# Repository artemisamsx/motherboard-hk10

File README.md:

# Artemisa MSX - Model HK-10 Motherboard

This repository contains the KiCad project files for the Model HK-10 motherboard, part of the **Artemisa** project.

## About Artemisa

Artemisa is a project to design new MSX-1 compatible computers using modern manufacturing
techniques while staying true to the original architecture: a Z80 CPU, discrete memory chips,
and dedicated peripheral ICs (VDP, PSG, PPI, etc.), with no FPGAs involved. The roadmap
includes several different models, each exploring different trade-offs between fidelity,
cost, and ease of assembly.

## The HK-10 model

The HK-10 is based on the **Model 101**, a prototype that was never distributed commercially.
The goal of the HK-10 is to bring that design to the general public as a homebrew-friendly
product, with the constraints and trade-offs typical of the homebrew scene.

"HK" stands for **Homebrew Kit**. The HK-10 is meant to be sold as a kit and assembled by the
user, comprising:

- The motherboard and other PCBs
- A 3D-printed PETG enclosure
- The main chips (CPU, memory, PSG, VDP)
- Passive components (resistors, capacitors, etc.)

### Features

- 2 cartridge slots
- 1 datasette (cassette) port
- 2 joystick ports
- External, cable-connected keyboard port

The HK-10 does **not** include a serial port or a printer port.

### Graphics

The graphics subsystem is implemented on separate PCBs rather than being part of the
motherboard itself, so that users can customize their video output and choose a graphics
chip (TMS9918 vs TMS9928 vs TMS9929). These graphics cards are based on the GFX-9918 card
used in the Model 101 prototype, but with a different form factor and naming, e.g.
`HKG-9918`, `HKG-9929`.

### Memory

The HK-10 uses SRAM instead of DRAM. For the memory sizes involved, SRAM is simpler, cheaper
and easier to source than DRAM, at the cost of some board space.

### Design philosophy

The HK-10 aims to be the simplest and most didactic model in the Artemisa lineup. To that
end, it avoids any programmable logic devices (PLDs, PALs, GALs, etc.) in favor of discrete
logic chips, consistent with how the original MSX computers were designed in the 1980s.

### Differences from the Model 101 prototype

- **Form factor**: the HK-10 uses a different, more compact form factor than the 101.
- **Power supply**: the HK-10 has its own integrated AC/DC adapter providing 5V, 12V and -12V,
  whereas the 101 was only powered externally at 5V.
- **Simplified circuits**: some circuits have been simplified compared to the 101, namely the
  clock generation and the power-on reset (PoR) circuit.
- **No integrated keyboard**: unlike most MSX computers (and most microcomputers of that era),
  the HK-10 does not have a keyboard built into the case. The keyboard is a separate unit
  connected via cable to a port on the motherboard.

## Repository layout

The schematic is split into sheets by functional block:

| File | Contents |
|---|---|
| `motherboard-hk10.kicad_sch` | Top-level sheet |
| `cpu.kicad_sch` | Z80 CPU |
| `ram.kicad_sch` | SRAM |
| `rom.kicad_sch` | ROM |
| `ppi.kicad_sch` | Programmable Peripheral Interface (keyboard, joysticks, cassette control) |
| `psg.kicad_sch` | Programmable Sound Generator |
| `clock.kicad_sch` | Clock generation |
| `decoding.kicad_sch` | Address decoding |
| `power.kicad_sch` | Power supply and power-on reset |
| `slots.kicad_sch` | Cartridge slots |
| `keyboard.kicad_sch` | External keyboard connector |
| `cassette.kicad_sch` | Datasette port |

`motherboard-hk10.kicad_pcb` contains the PCB layout, and `simulation/` contains SPICE
simulations used to validate specific circuits (power-on reset, clock generation, video
output filtering, etc.).

See [CHANGELOG.md](CHANGELOG.md) for a history of board revisions.

## Key components

- **Clock generator**: [Epson SG-615P / SG-531P][1], a packaged crystal oscillator (SPXO)
  used to generate the master clock.

## License

This project is licensed under the [TAPR Open Hardware License](LICENSE.txt).

---

[1]: https://www.mouser.com/datasheet/2/137/SG_615P_en-1880245.pdf "Epson SG-615P / SG-531P datasheet"

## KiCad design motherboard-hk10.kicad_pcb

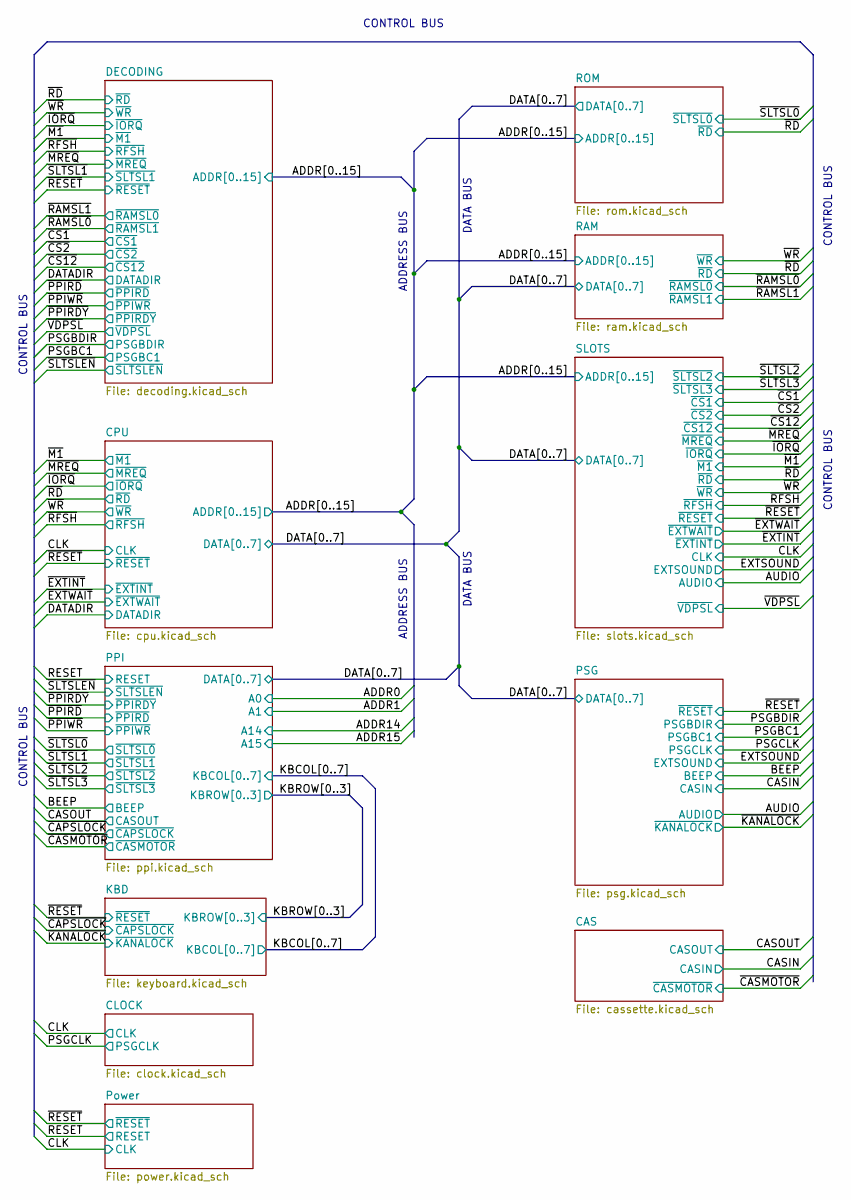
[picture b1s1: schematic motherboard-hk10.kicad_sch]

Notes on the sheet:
CONTROL BUS
ADDRESS BUS
DATA BUS

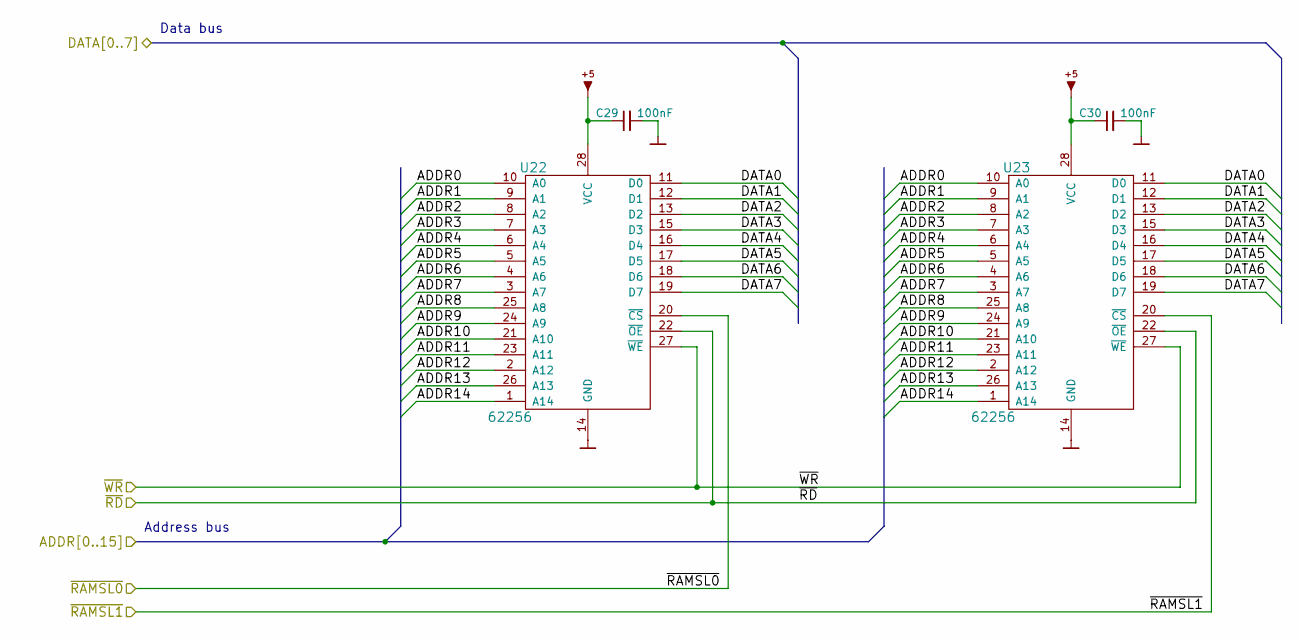
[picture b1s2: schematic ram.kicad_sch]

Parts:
C29, C30: 100nF; C_Disc_D5.0mm_W2.5mm_P2.50mm
U22, U23: 62256; DIP-28_W15.24mm_Socket

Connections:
/ADDR0: U22.10 (A0), U23.10 (A0); also elsewhere on the board
/ADDR1: U22.9 (A1), U23.9 (A1); also elsewhere on the board
/ADDR2: U22.8 (A2), U23.8 (A2); also elsewhere on the board
/ADDR3: U22.7 (A3), U23.7 (A3); also elsewhere on the board
/ADDR4: U22.6 (A4), U23.6 (A4); also elsewhere on the board
/ADDR5: U22.5 (A5), U23.5 (A5); also elsewhere on the board
/ADDR6: U22.4 (A6), U23.4 (A6); also elsewhere on the board
/ADDR7: U22.3 (A7), U23.3 (A7); also elsewhere on the board
/ADDR8: U22.25 (A8), U23.25 (A8); also elsewhere on the board
/ADDR9: U22.24 (A9), U23.24 (A9); also elsewhere on the board
/ADDR10: U22.21 (A10), U23.21 (A10); also elsewhere on the board
/ADDR11: U22.23 (A11), U23.23 (A11); also elsewhere on the board
/ADDR12: U22.2 (A12), U23.2 (A12); also elsewhere on the board
/ADDR13: U22.26 (A13), U23.26 (A13); also elsewhere on the board
/ADDR14: U22.1 (A14), U23.1 (A14); also elsewhere on the board
/DATA0: U22.11 (D0), U23.11 (D0); also elsewhere on the board
/DATA1: U22.12 (D1), U23.12 (D1); also elsewhere on the board
/DATA2: U22.13 (D2), U23.13 (D2); also elsewhere on the board
/DATA3: U22.15 (D3), U23.15 (D3); also elsewhere on the board
/DATA4: U22.16 (D4), U23.16 (D4); also elsewhere on the board
/DATA5: U22.17 (D5), U23.17 (D5); also elsewhere on the board
/DATA6: U22.18 (D6), U23.18 (D6); also elsewhere on the board
/DATA7: U22.19 (D7), U23.19 (D7); also elsewhere on the board
/~RAMSL0: U22.20 (~CS); also elsewhere on the board
/~RAMSL1: U23.20 (~CS); also elsewhere on the board
/~RD: U22.22 (~OE), U23.22 (~OE); also elsewhere on the board
/~WR: U22.27 (~WE), U23.27 (~WE); also elsewhere on the board
GND: C29.2, C30.2, U22.14 (GND), U23.14 (GND); also elsewhere on the board
VCC: C29.1, C30.1, U22.28 (VCC), U23.28 (VCC); also elsewhere on the board

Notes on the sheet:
Data bus
Address bus

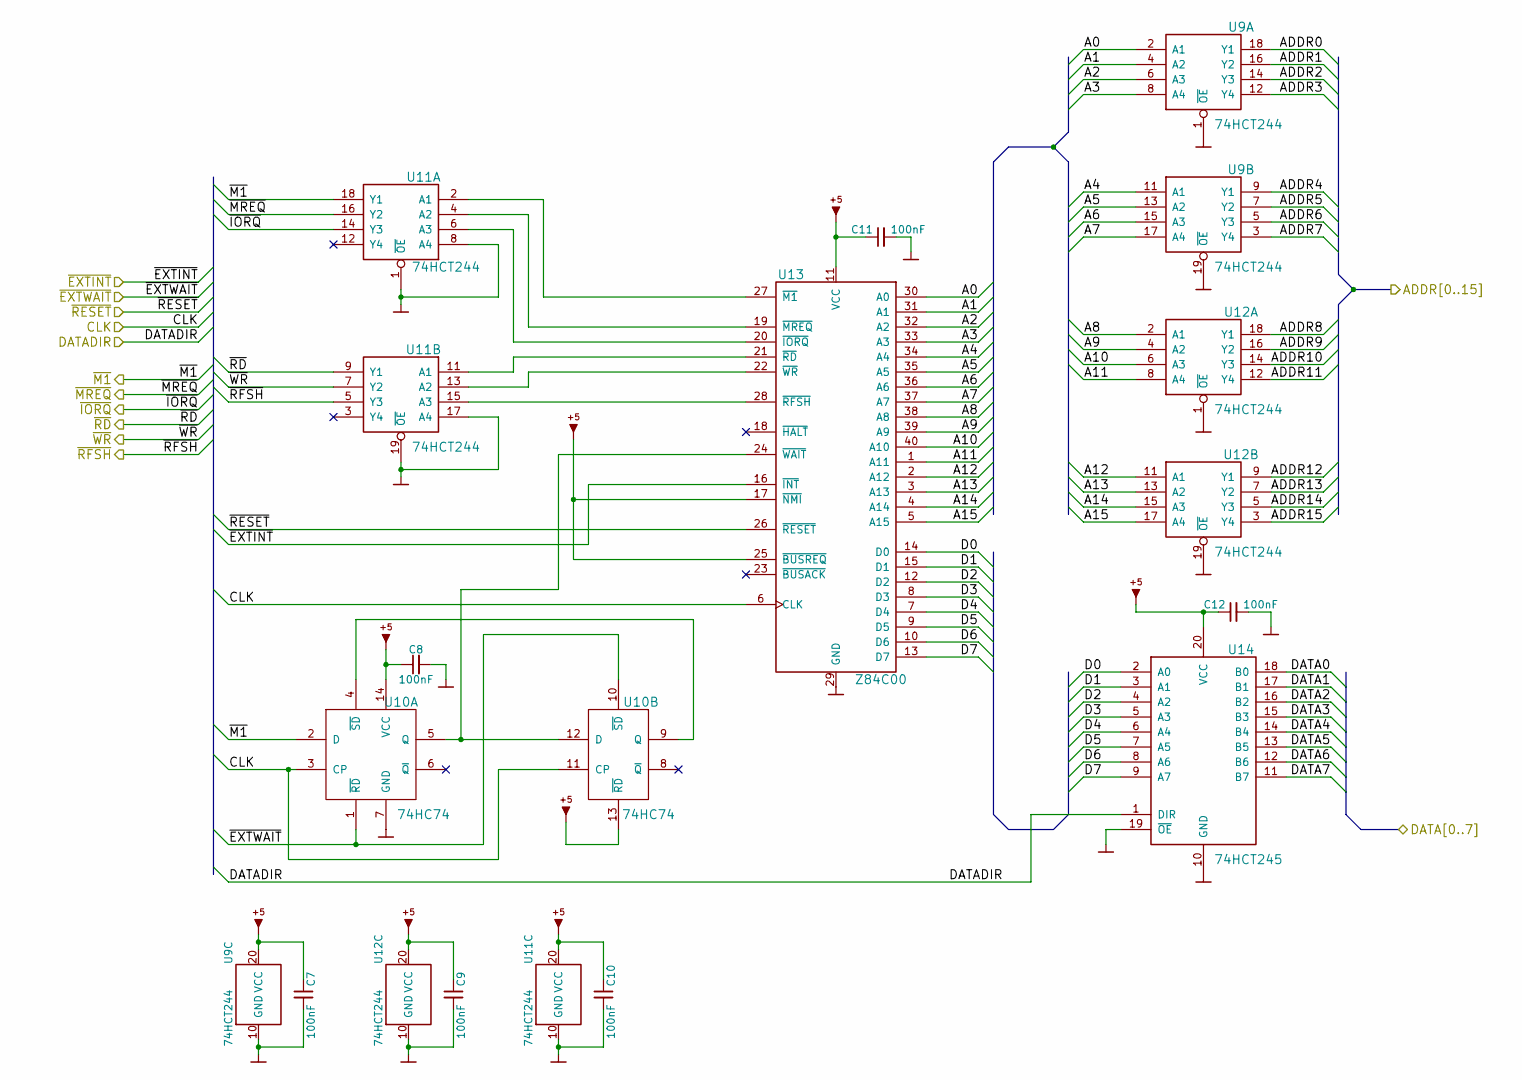
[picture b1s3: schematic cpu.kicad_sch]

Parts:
C7, C8, C9, C10, C11, C12: 100nF; C_Disc_D5.0mm_W2.5mm_P2.50mm
U9, U11, U12: 74HCT244; DIP-20_W7.62mm
U10: 74HC74; DIP-14_W7.62mm
U13: Z84C00; DIP-40_W15.24mm_Socket
U14: 74HCT245; DIP-20_W7.62mm

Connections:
/ADDR0: U9.18 (Y1); also elsewhere on the board
/ADDR1: U9.16 (Y2); also elsewhere on the board
/ADDR2: U9.14 (Y3); also elsewhere on the board
/ADDR3: U9.12 (Y4); also elsewhere on the board
/ADDR4: U9.9 (Y1); also elsewhere on the board
/ADDR5: U9.7 (Y2); also elsewhere on the board
/ADDR6: U9.5 (Y3); also elsewhere on the board
/ADDR7: U9.3 (Y4); also elsewhere on the board
/ADDR8: U12.18 (Y1); also elsewhere on the board
/ADDR9: U12.16 (Y2); also elsewhere on the board
/ADDR10: U12.14 (Y3); also elsewhere on the board
/ADDR11: U12.12 (Y4); also elsewhere on the board
/ADDR12: U12.9 (Y1); also elsewhere on the board
/ADDR13: U12.7 (Y2); also elsewhere on the board
/ADDR14: U12.5 (Y3); also elsewhere on the board
/ADDR15: U12.3 (Y4); also elsewhere on the board
/CLK: U10.3 (CP), U10.11 (CP), U13.6 (CLK); also elsewhere on the board
/CPU/A0: U9.2 (A1), U13.30 (A0)
/CPU/A1: U9.4 (A2), U13.31 (A1)
/CPU/A2: U9.6 (A3), U13.32 (A2)
/CPU/A3: U9.8 (A4), U13.33 (A3)
/CPU/A4: U9.11 (A1), U13.34 (A4)
/CPU/A5: U9.13 (A2), U13.35 (A5)
/CPU/A6: U9.15 (A3), U13.36 (A6)
/CPU/A7: U9.17 (A4), U13.37 (A7)
/CPU/A8: U12.2 (A1), U13.38 (A8)
/CPU/A9: U12.4 (A2), U13.39 (A9)
/CPU/A10: U12.6 (A3), U13.40 (A10)
/CPU/A11: U12.8 (A4), U13.1 (A11)
/CPU/A12: U12.11 (A1), U13.2 (A12)
/CPU/A13: U12.13 (A2), U13.3 (A13)
/CPU/A14: U12.15 (A3), U13.4 (A14)
/CPU/A15: U12.17 (A4), U13.5 (A15)
/CPU/D0: U13.14 (D0), U14.2 (A0)
/CPU/D1: U13.15 (D1), U14.3 (A1)
/CPU/D2: U13.12 (D2), U14.4 (A2)
/CPU/D3: U13.8 (D3), U14.5 (A3)
/CPU/D4: U13.7 (D4), U14.6 (A4)
/CPU/D5: U13.9 (D5), U14.7 (A5)
/CPU/D6: U13.10 (D6), U14.8 (A6)
/CPU/D7: U13.13 (D7), U14.9 (A7)
/DATA0: U14.18 (B0); also elsewhere on the board
/DATA1: U14.17 (B1); also elsewhere on the board
/DATA2: U14.16 (B2); also elsewhere on the board
/DATA3: U14.15 (B3); also elsewhere on the board
/DATA4: U14.14 (B4); also elsewhere on the board
/DATA5: U14.13 (B5); also elsewhere on the board
/DATA6: U14.12 (B6); also elsewhere on the board
/DATA7: U14.11 (B7); also elsewhere on the board
/DATADIR: U14.1 (DIR); also elsewhere on the board
/~EXTINT: U13.16 (~INT); also elsewhere on the board
/~EXTWAIT: U10.1 (~RD), U10.10 (~SD); also elsewhere on the board
/~IORQ: U11.14 (Y3); also elsewhere on the board
/~M1: U10.2 (D), U11.18 (Y1); also elsewhere on the board
/~MREQ: U11.16 (Y2); also elsewhere on the board
/~RD: U11.9 (Y1); also elsewhere on the board
/~RESET: U13.26 (~RESET); also elsewhere on the board
/~RFSH: U11.5 (Y3); also elsewhere on the board
/~WR: U11.7 (Y2); also elsewhere on the board
GND: C7.2, C8.2, C9.2, C10.2, C11.2, C12.2, U9.1 (~OE), U9.10 (GND), U9.19 (~OE), U10.7 (GND), U11.1 (~OE), U11.8 (A4), U11.10 (GND), U11.17 (A4), U11.19 (~OE), U12.1 (~OE), U12.10 (GND), U12.19 (~OE), U13.29 (GND), U14.10 (GND), U14.19 (~OE); also elsewhere on the board
unnamed: U10.5 (Q), U10.12 (D), U13.24 (~WAIT)
unnamed: U10.4 (~SD), U10.9 (Q)
unnamed: U11.2 (A1), U13.27 (~M1)
unnamed: U11.4 (A2), U13.19 (~MREQ)
unnamed: U11.6 (A3), U13.20 (~IORQ)
unnamed: U11.11 (A1), U13.21 (~RD)
unnamed: U11.13 (A2), U13.22 (~WR)
unnamed: U11.15 (A3), U13.28 (~RFSH)
VCC: C7.1, C8.1, C9.1, C10.1, C11.1, C12.1, U9.20 (VCC), U10.13 (~RD), U10.14 (VCC), U11.20 (VCC), U12.20 (VCC), U13.11 (VCC), U13.17 (~NMI), U13.25 (~BUSREQ), U14.20 (VCC); also elsewhere on the board

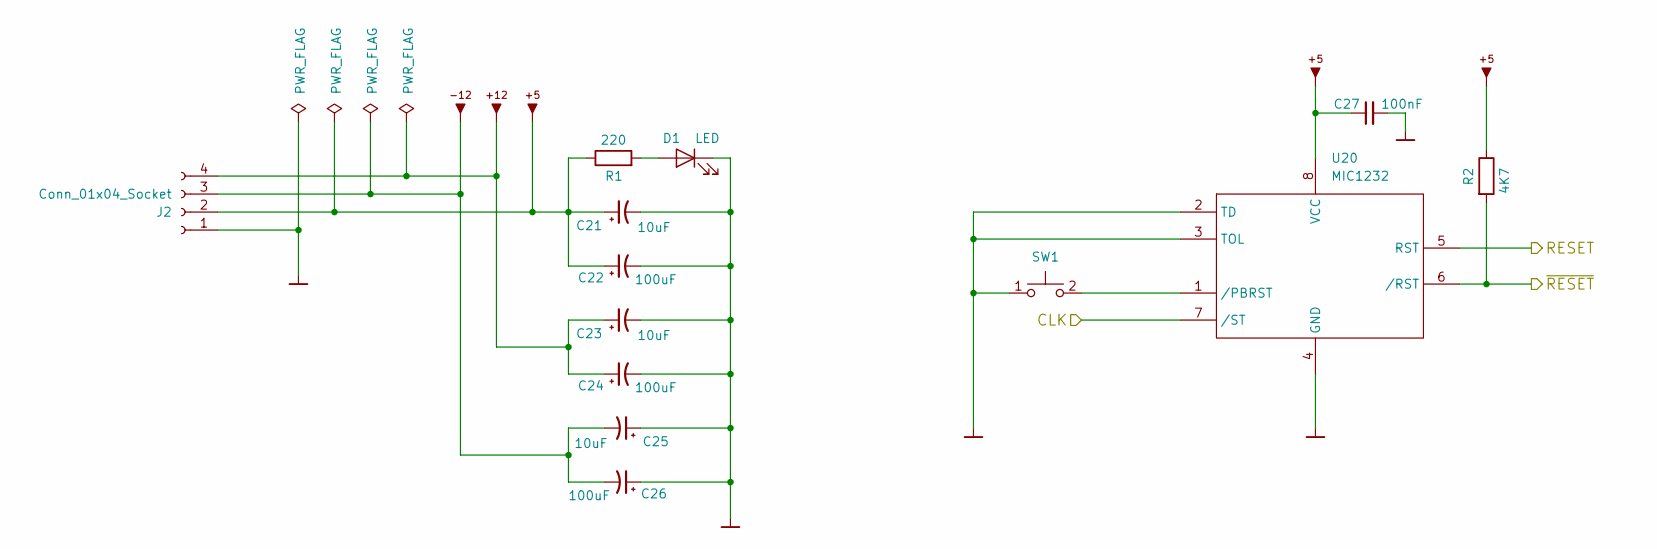
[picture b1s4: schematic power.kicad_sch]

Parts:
C21, C23, C25: 10uF; CP_Radial_D4.0mm_P2.00mm
C22, C24, C26: 100uF; CP_Radial_D5.0mm_P2.50mm
C27: 100nF; C_Disc_D5.0mm_W2.5mm_P2.50mm
D1: LED; PinHeader_1x02_P2.54mm_Vertical
J2: Conn_01x04_Socket; JST_XH_B4B-XH-A_1x04_P2.50mm_Vertical
R1: 220; R_Axial_DIN0207_L6.3mm_D2.5mm_P10.16mm_Horizontal
R2: 4K7; R_Axial_DIN0207_L6.3mm_D2.5mm_P10.16mm_Horizontal
SW1: Push_button; Push_button_angled
U20: MIC1232; DIP-8_W7.62mm

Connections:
12V: C23.1, C24.1, J2.4; also elsewhere on the board
-12V: C25.2, C26.2, J2.3; also elsewhere on the board
/CLK: U20.7 (/ST); also elsewhere on the board
/RESET: U20.5 (RST); also elsewhere on the board
/~RESET: R2.2, U20.6 (/RST); also elsewhere on the board
GND: C21.2, C22.2, C23.2, C24.2, C25.1, C26.1, C27.2, D1.2 (K), J2.1, SW1.1, U20.2 (TD), U20.3 (TOL), U20.4 (GND); also elsewhere on the board
unnamed: D1.1 (A), R1.2
unnamed: SW1.2, U20.1 (/PBRST)
VCC: C21.1, C22.1, C27.1, J2.2, R1.1, R2.1, U20.8 (VCC); also elsewhere on the board

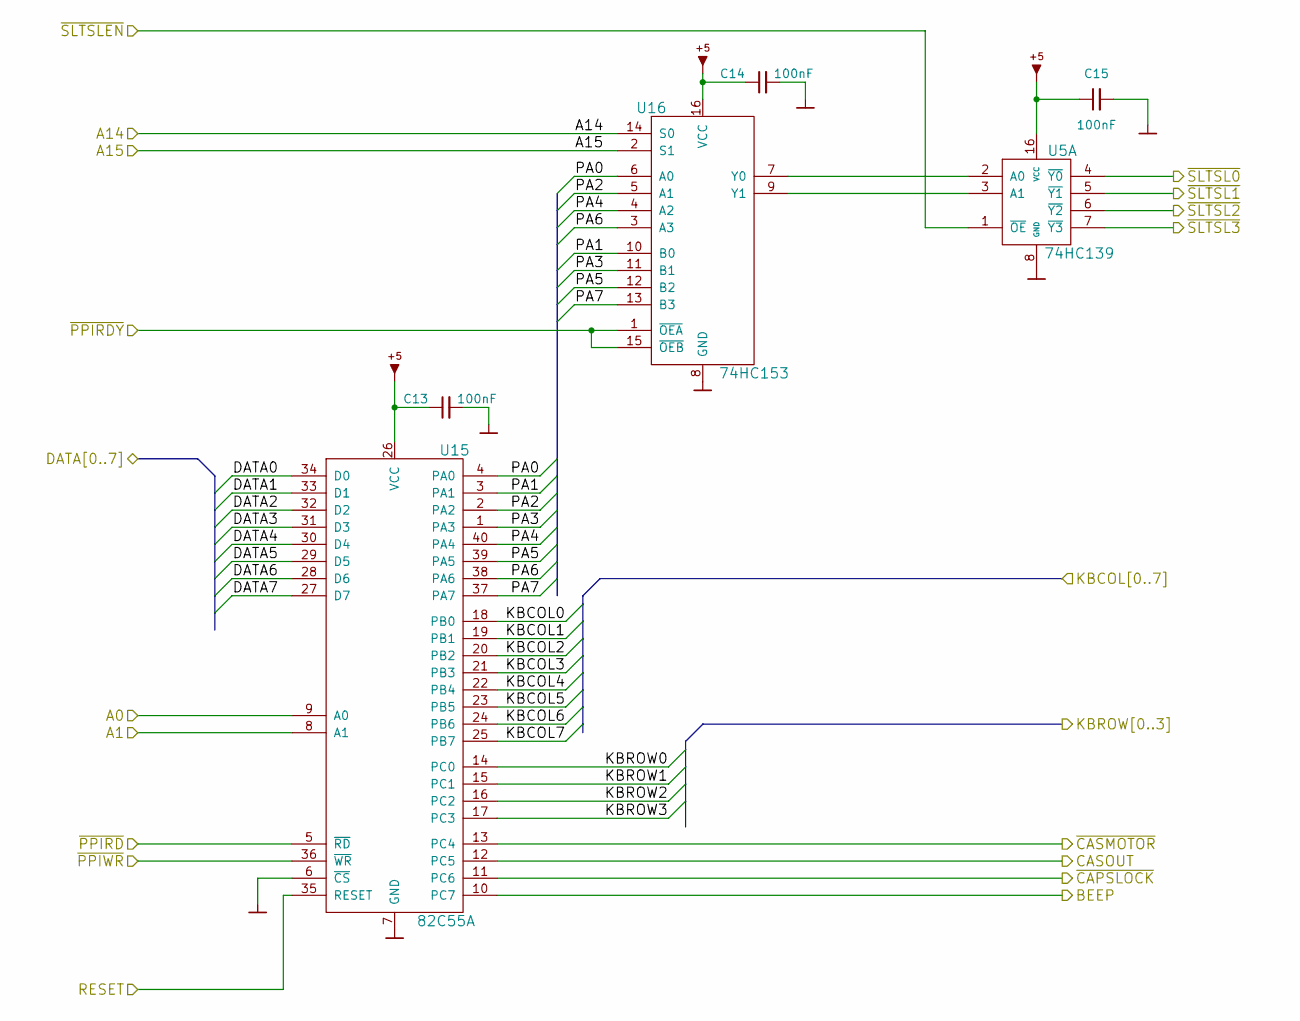
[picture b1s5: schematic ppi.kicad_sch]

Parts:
C13, C14, C15: 100nF; C_Disc_D5.0mm_W2.5mm_P2.50mm
U5: 74HC139; DIP-16_W7.62mm
U15: 82C55A; DIP-40_W15.24mm_Socket
U16: 74HC153; DIP-16_W7.62mm

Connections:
/ADDR0: U15.9 (A0); also elsewhere on the board
/ADDR1: U15.8 (A1); also elsewhere on the board
/ADDR14: U16.14 (S0); also elsewhere on the board
/ADDR15: U16.2 (S1); also elsewhere on the board
/BEEP: U15.10 (PC7); also elsewhere on the board
/CASOUT: U15.12 (PC5); also elsewhere on the board
/DATA0: U15.34 (D0); also elsewhere on the board
/DATA1: U15.33 (D1); also elsewhere on the board
/DATA2: U15.32 (D2); also elsewhere on the board
/DATA3: U15.31 (D3); also elsewhere on the board
/DATA4: U15.30 (D4); also elsewhere on the board
/DATA5: U15.29 (D5); also elsewhere on the board
/DATA6: U15.28 (D6); also elsewhere on the board
/DATA7: U15.27 (D7); also elsewhere on the board
/KBCOL0: U15.18 (PB0); also elsewhere on the board
/KBCOL1: U15.19 (PB1); also elsewhere on the board
/KBCOL2: U15.20 (PB2); also elsewhere on the board
/KBCOL3: U15.21 (PB3); also elsewhere on the board
/KBCOL4: U15.22 (PB4); also elsewhere on the board
/KBCOL5: U15.23 (PB5); also elsewhere on the board
/KBCOL6: U15.24 (PB6); also elsewhere on the board
/KBCOL7: U15.25 (PB7); also elsewhere on the board
/KBROW0: U15.14 (PC0); also elsewhere on the board
/KBROW1: U15.15 (PC1); also elsewhere on the board
/KBROW2: U15.16 (PC2); also elsewhere on the board
/KBROW3: U15.17 (PC3); also elsewhere on the board
/PPI/PA0: U15.4 (PA0), U16.6 (A0)
/PPI/PA1: U15.3 (PA1), U16.10 (B0)
/PPI/PA2: U15.2 (PA2), U16.5 (A1)
/PPI/PA3: U15.1 (PA3), U16.11 (B1)
/PPI/PA4: U15.40 (PA4), U16.4 (A2)
/PPI/PA5: U15.39 (PA5), U16.12 (B2)
/PPI/PA6: U15.38 (PA6), U16.3 (A3)
/PPI/PA7: U15.37 (PA7), U16.13 (B3)
/RESET: U15.35 (RESET); also elsewhere on the board
/~CAPSLOCK: U15.11 (PC6); also elsewhere on the board
/~CASMOTOR: U15.13 (PC4); also elsewhere on the board
/~PPIRDY: U16.1 (~OEA), U16.15 (~OEB); also elsewhere on the board
/~PPIRD: U15.5 (~RD); also elsewhere on the board
/~PPIWR: U15.36 (~WR); also elsewhere on the board
/~SLTSL0: U5.4 (~Y0); also elsewhere on the board
/~SLTSL1: U5.5 (~Y1); also elsewhere on the board
/~SLTSL2: U5.6 (~Y2); also elsewhere on the board
/~SLTSL3: U5.7 (~Y3); also elsewhere on the board
/~SLTSLEN: U5.1 (~OE); also elsewhere on the board
GND: C13.2, C14.2, C15.2, U5.8 (GND), U15.6 (~CS), U15.7 (GND), U16.8 (GND); also elsewhere on the board
unnamed: U5.2 (A0), U16.7 (Y0)
unnamed: U5.3 (A1), U16.9 (Y1)
VCC: C13.1, C14.1, C15.1, U5.16 (VCC), U15.26 (VCC), U16.16 (VCC); also elsewhere on the board

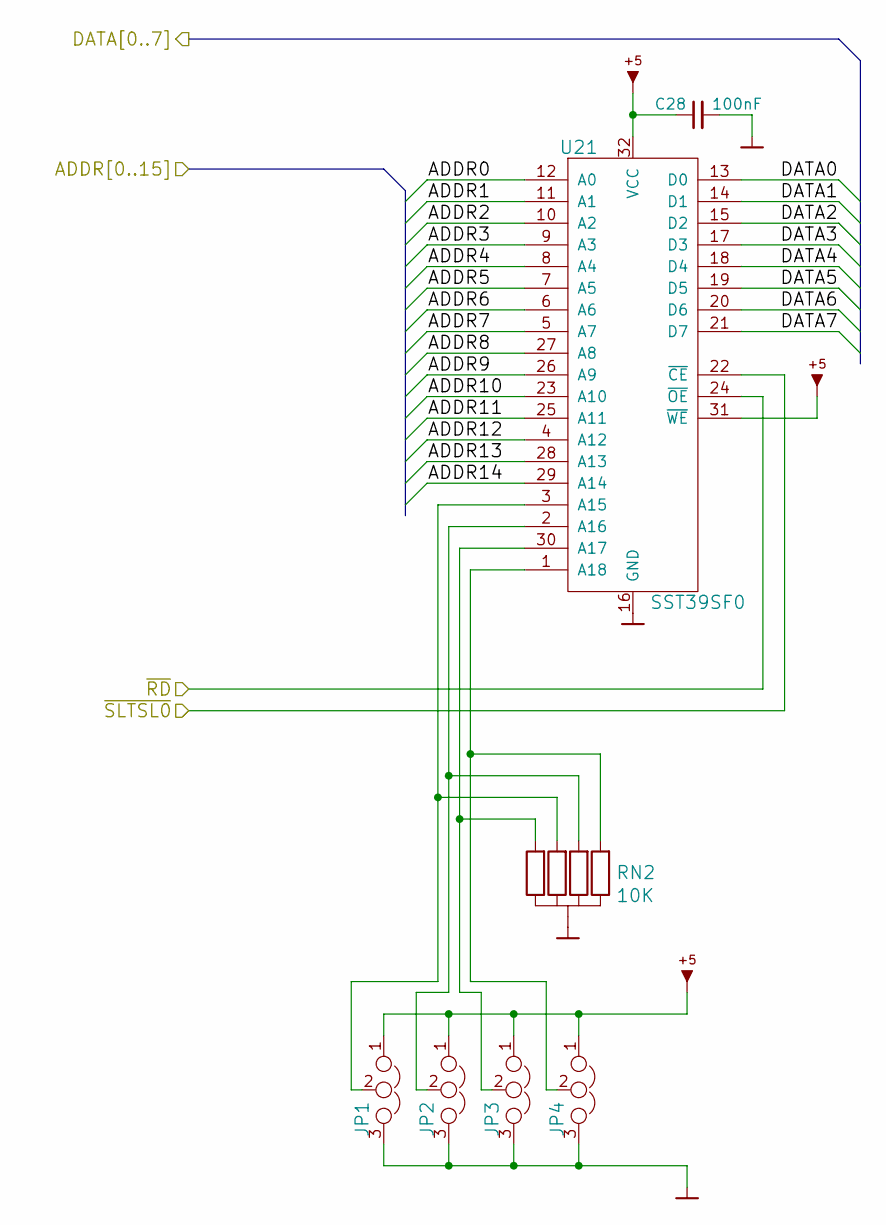
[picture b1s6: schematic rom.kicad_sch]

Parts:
C28: 100nF; C_Disc_D5.0mm_W2.5mm_P2.50mm
JP1, JP2, JP3, JP4: Jumper; PinHeader_1x03_P2.54mm_Vertical
RN2: 10K; R_Array_SIP5
U21: SST39SF0; DIP-32_W15.24mm_Socket

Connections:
/ADDR0: U21.12 (A0); also elsewhere on the board
/ADDR1: U21.11 (A1); also elsewhere on the board
/ADDR2: U21.10 (A2); also elsewhere on the board
/ADDR3: U21.9 (A3); also elsewhere on the board
/ADDR4: U21.8 (A4); also elsewhere on the board
/ADDR5: U21.7 (A5); also elsewhere on the board
/ADDR6: U21.6 (A6); also elsewhere on the board
/ADDR7: U21.5 (A7); also elsewhere on the board
/ADDR8: U21.27 (A8); also elsewhere on the board
/ADDR9: U21.26 (A9); also elsewhere on the board
/ADDR10: U21.23 (A10); also elsewhere on the board
/ADDR11: U21.25 (A11); also elsewhere on the board
/ADDR12: U21.4 (A12); also elsewhere on the board
/ADDR13: U21.28 (A13); also elsewhere on the board
/ADDR14: U21.29 (A14); also elsewhere on the board
/DATA0: U21.13 (D0); also elsewhere on the board
/DATA1: U21.14 (D1); also elsewhere on the board
/DATA2: U21.15 (D2); also elsewhere on the board
/DATA3: U21.17 (D3); also elsewhere on the board
/DATA4: U21.18 (D4); also elsewhere on the board
/DATA5: U21.19 (D5); also elsewhere on the board
/DATA6: U21.20 (D6); also elsewhere on the board
/DATA7: U21.21 (D7); also elsewhere on the board
/~RD: U21.24 (~OE); also elsewhere on the board
/~SLTSL0: U21.22 (~CE); also elsewhere on the board
GND: C28.2, JP1.3, JP2.3, JP3.3, JP4.3, RN2.1, U21.16 (GND); also elsewhere on the board
unnamed: JP1.2, RN2.4, U21.3 (A15)
unnamed: JP2.2, RN2.3, U21.2 (A16)
unnamed: JP3.2, RN2.5, U21.30 (A17)
unnamed: JP4.2, RN2.2, U21.1 (A18)
VCC: C28.1, JP1.1, JP2.1, JP3.1, JP4.1, U21.31 (~WE), U21.32 (VCC); also elsewhere on the board

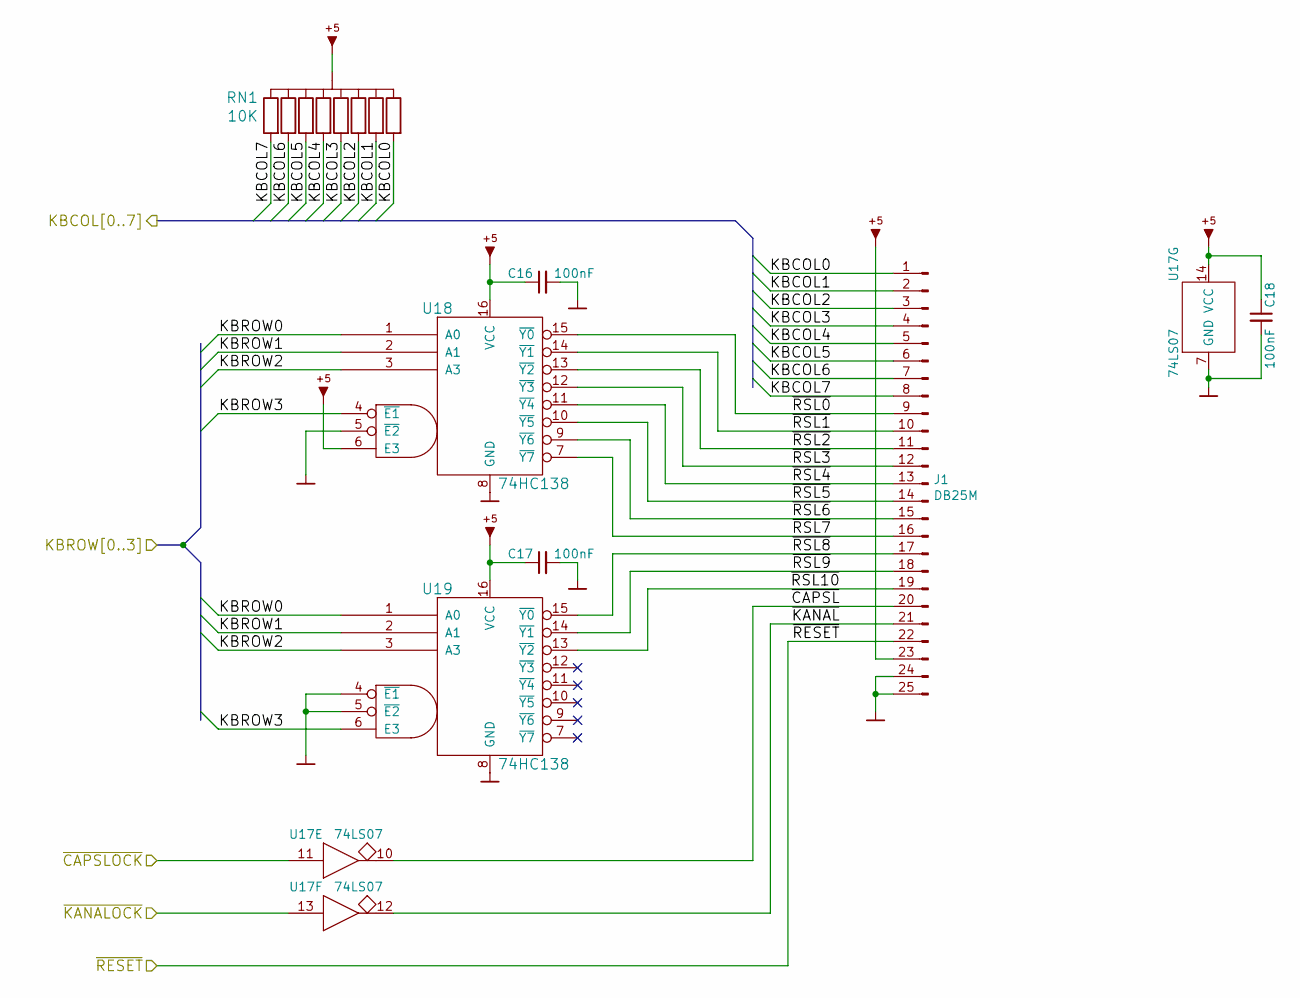
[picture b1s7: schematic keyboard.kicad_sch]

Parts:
C16, C17, C18: 100nF; C_Disc_D5.0mm_W2.5mm_P2.50mm
J1: DB25M
RN1: 10K; R_Array_SIP9
U17: 74LS07; DIP-14_W7.62mm
U18, U19: 74HC138; DIP-16_W7.62mm

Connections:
/KBCOL0: J1.1, RN1.2; also elsewhere on the board
/KBCOL1: J1.2, RN1.3; also elsewhere on the board
/KBCOL2: J1.3, RN1.4; also elsewhere on the board
/KBCOL3: J1.4, RN1.5; also elsewhere on the board
/KBCOL4: J1.5, RN1.6; also elsewhere on the board
/KBCOL5: J1.6, RN1.7; also elsewhere on the board
/KBCOL6: J1.7, RN1.8; also elsewhere on the board
/KBCOL7: J1.8, RN1.9; also elsewhere on the board
/KBD/~CAPSL: J1.20, U17.10
/KBD/~KANAL: J1.21, U17.12
/KBD/~RSL0: J1.9, U18.15 (~Y0)
/KBD/~RSL1: J1.10, U18.14 (~Y1)
/KBD/~RSL2: J1.11, U18.13 (~Y2)
/KBD/~RSL3: J1.12, U18.12 (~Y3)
/KBD/~RSL4: J1.13, U18.11 (~Y4)
/KBD/~RSL5: J1.14, U18.10 (~Y5)
/KBD/~RSL6: J1.15, U18.9 (~Y6)
/KBD/~RSL7: J1.16, U18.7 (~Y7)
/KBD/~RSL8: J1.17, U19.15 (~Y0)
/KBD/~RSL9: J1.18, U19.14 (~Y1)
/KBD/~RSL10: J1.19, U19.13 (~Y2)
/KBROW0: U18.1 (A0), U19.1 (A0); also elsewhere on the board
/KBROW1: U18.2 (A1), U19.2 (A1); also elsewhere on the board
/KBROW2: U18.3 (A3), U19.3 (A3); also elsewhere on the board
/KBROW3: U18.4 (~E1), U19.6 (E3); also elsewhere on the board
/~CAPSLOCK: U17.11; also elsewhere on the board
/~KANALOCK: U17.13; also elsewhere on the board
/~RESET: J1.22; also elsewhere on the board
GND: C16.2, C17.2, C18.2, J1.24, J1.25, U17.7 (GND), U18.5 (~E2), U18.8 (GND), U19.4 (~E1), U19.5 (~E2), U19.8 (GND); also elsewhere on the board
VCC: C16.1, C17.1, C18.1, J1.23, RN1.1, U17.14 (VCC), U18.6 (E3), U18.16 (VCC), U19.16 (VCC); also elsewhere on the board

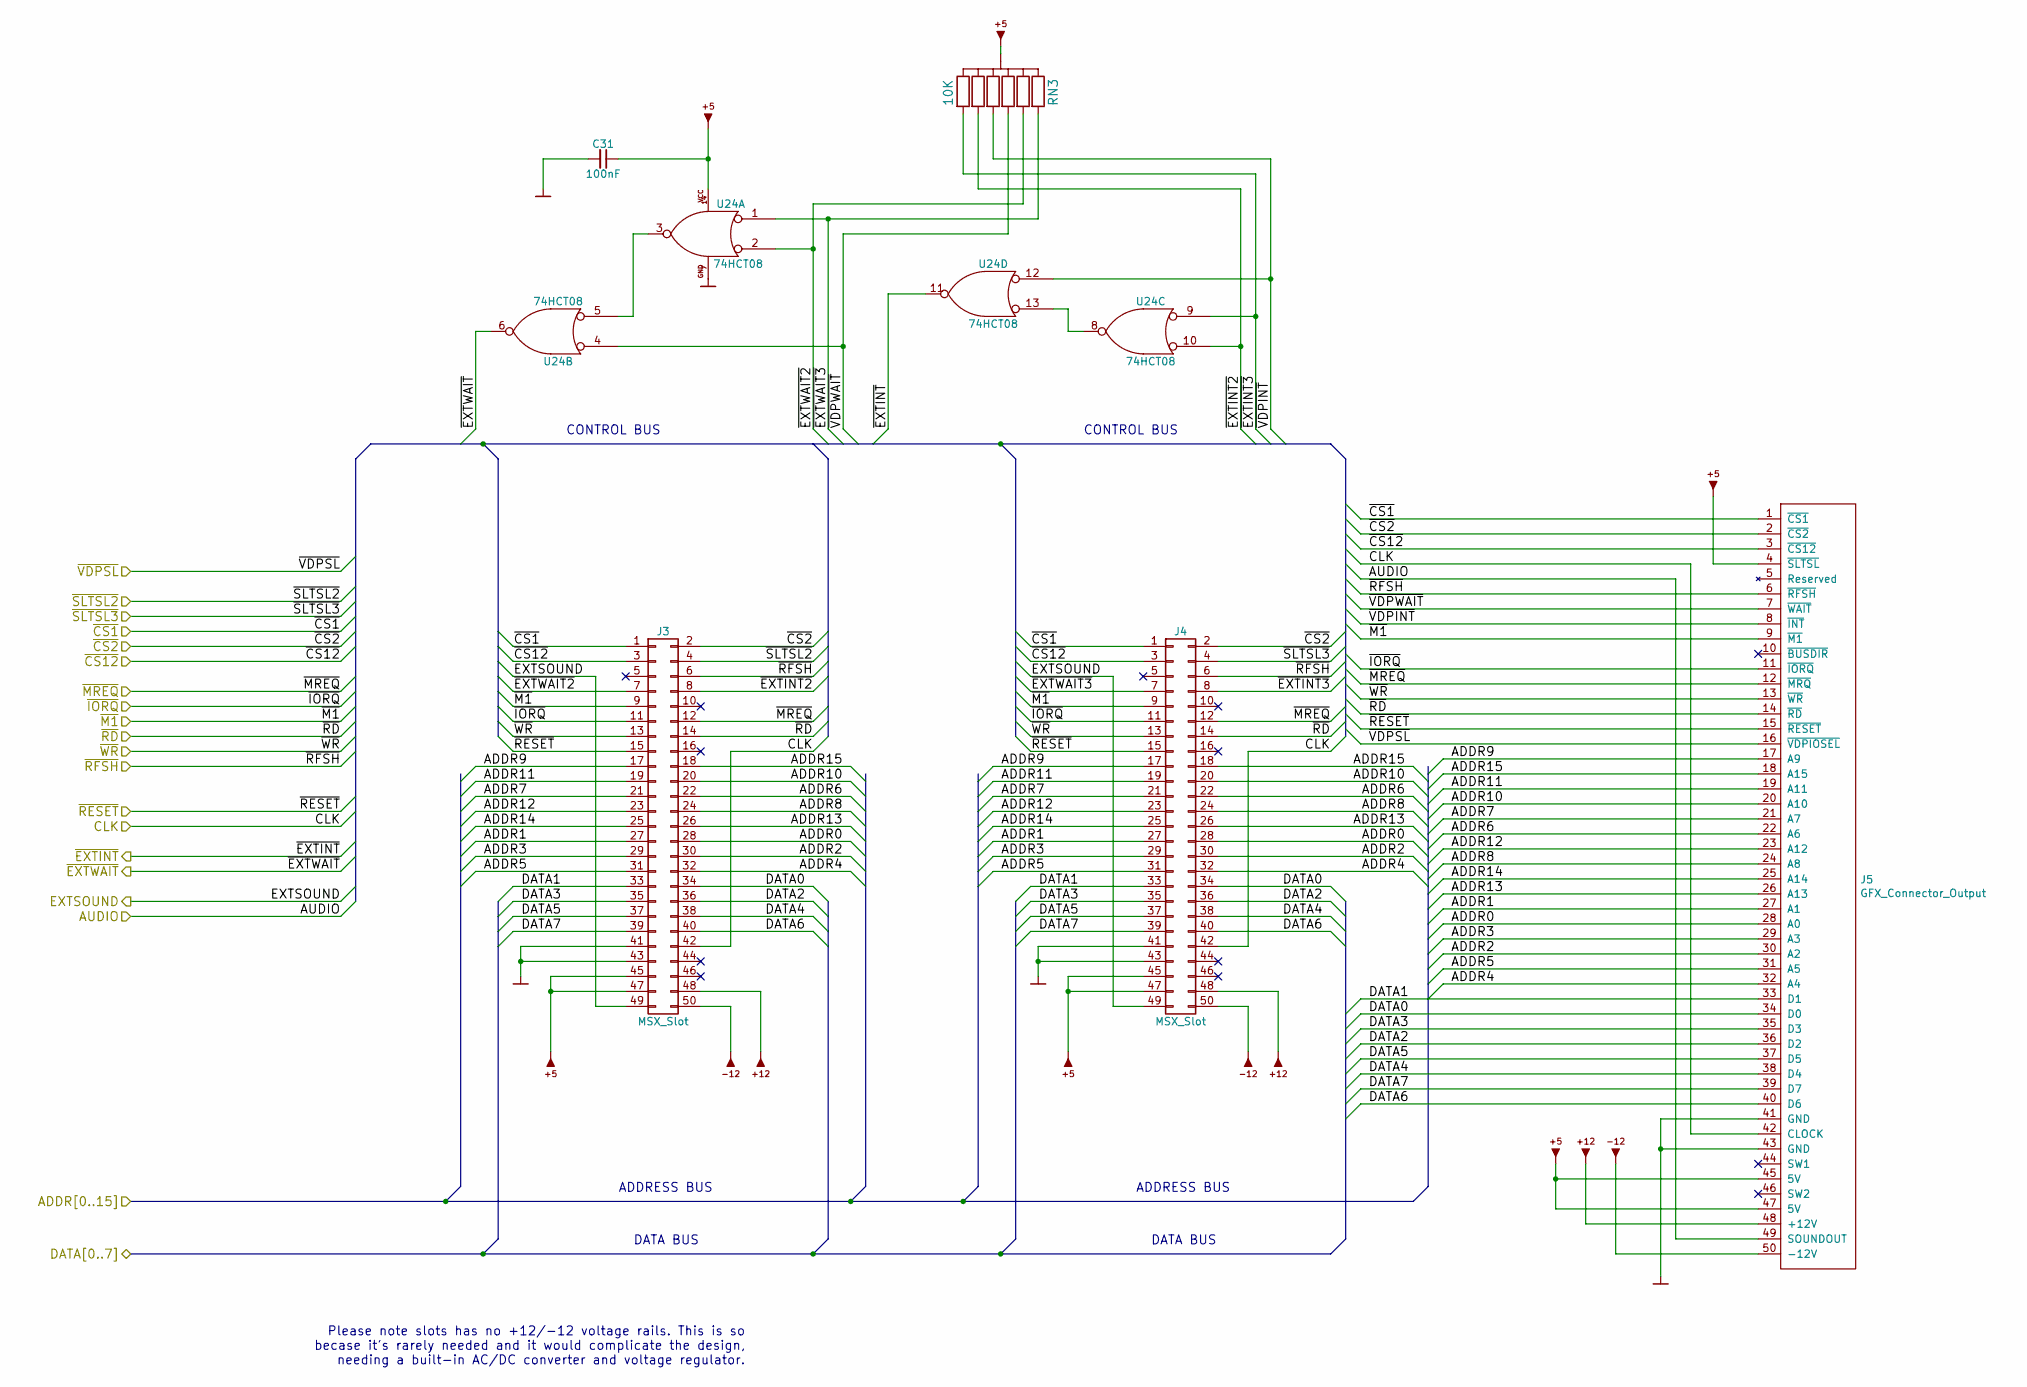
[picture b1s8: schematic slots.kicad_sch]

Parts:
C31: 100nF; C_Disc_D5.0mm_W2.5mm_P2.50mm
J3, J4: MSX_Slot; Slot_conn
J5: GFX_Connector_Output; IDC-Header_2x25_P2.54mm_Vertical
RN3: 10K; R_Array_SIP7
U24: 74HCT08; DIP-14_W7.62mm

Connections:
12V: J3.48, J4.48, J5.48 (+12V); also elsewhere on the board
-12V: J3.50, J4.50, J5.50 (-12V); also elsewhere on the board
/ADDR0: J3.28, J4.28, J5.28 (A0); also elsewhere on the board
/ADDR1: J3.27, J4.27, J5.27 (A1); also elsewhere on the board
/ADDR2: J3.30, J4.30, J5.30 (A2); also elsewhere on the board
/ADDR3: J3.29, J4.29, J5.29 (A3); also elsewhere on the board
/ADDR4: J3.32, J4.32, J5.32 (A4); also elsewhere on the board
/ADDR5: J3.31, J4.31, J5.31 (A5); also elsewhere on the board
/ADDR6: J3.22, J4.22, J5.22 (A6); also elsewhere on the board
/ADDR7: J3.21, J4.21, J5.21 (A7); also elsewhere on the board
/ADDR8: J3.24, J4.24, J5.24 (A8); also elsewhere on the board
/ADDR9: J3.17, J4.17, J5.17 (A9); also elsewhere on the board
/ADDR10: J3.20, J4.20, J5.20 (A10); also elsewhere on the board
/ADDR11: J3.19, J4.19, J5.19 (A11); also elsewhere on the board
/ADDR12: J3.23, J4.23, J5.23 (A12); also elsewhere on the board
/ADDR13: J3.26, J4.26, J5.26 (A13); also elsewhere on the board
/ADDR14: J3.25, J4.25, J5.25 (A14); also elsewhere on the board
/ADDR15: J3.18, J4.18, J5.18 (A15); also elsewhere on the board
/AUDIO: J5.49 (SOUNDOUT); also elsewhere on the board
/CLK: J3.42, J4.42, J5.42 (CLOCK); also elsewhere on the board
/DATA0: J3.34, J4.34, J5.34 (D0); also elsewhere on the board
/DATA1: J3.33, J4.33, J5.33 (D1); also elsewhere on the board
/DATA2: J3.36, J4.36, J5.36 (D2); also elsewhere on the board
/DATA3: J3.35, J4.35, J5.35 (D3); also elsewhere on the board
/DATA4: J3.38, J4.38, J5.38 (D4); also elsewhere on the board
/DATA5: J3.37, J4.37, J5.37 (D5); also elsewhere on the board
/DATA6: J3.40, J4.40, J5.40 (D6); also elsewhere on the board
/DATA7: J3.39, J4.39, J5.39 (D7); also elsewhere on the board
/EXTSOUND: J3.49, J4.49; also elsewhere on the board
/SLOTS/~EXTINT2: J3.8, RN3.3, U24.10
/SLOTS/~EXTINT3: J4.8, RN3.2, U24.9
/SLOTS/~EXTWAIT2: J3.7, RN3.6, U24.2
/SLOTS/~EXTWAIT3: J4.7, RN3.7, U24.1
/SLOTS/~VDPINT: J5.8 (~INT), RN3.4, U24.12
/SLOTS/~VDPWAIT: J5.7 (~WAIT), RN3.5, U24.4
/~CS1: J3.1, J4.1, J5.1 (~CS1); also elsewhere on the board
/~CS2: J3.2, J4.2, J5.2 (~CS2); also elsewhere on the board
/~CS12: J3.3, J4.3, J5.3 (~CS12); also elsewhere on the board
/~EXTINT: U24.11; also elsewhere on the board
/~EXTWAIT: U24.6; also elsewhere on the board
/~IORQ: J3.11, J4.11, J5.11 (~IORQ); also elsewhere on the board
/~M1: J3.9, J4.9, J5.9 (~M1); also elsewhere on the board
/~MREQ: J3.12, J4.12, J5.12 (~MRQ); also elsewhere on the board
/~RD: J3.14, J4.14, J5.14 (~RD); also elsewhere on the board
/~RESET: J3.15, J4.15, J5.15 (~RESET); also elsewhere on the board
/~RFSH: J3.6, J4.6, J5.6 (~RFSH); also elsewhere on the board
/~SLTSL2: J3.4; also elsewhere on the board
/~SLTSL3: J4.4; also elsewhere on the board
/~VDPSL: J5.16 (~VDPIOSEL); also elsewhere on the board
/~WR: J3.13, J4.13, J5.13 (~WR); also elsewhere on the board
GND: C31.2, J3.41, J3.43, J4.41, J4.43, J5.41 (GND), J5.43 (GND), U24.7 (GND); also elsewhere on the board
unnamed: U24.3, U24.5
unnamed: U24.8, U24.13
VCC: C31.1, J3.45, J3.47, J4.45, J4.47, J5.4 (~SLTSL), J5.45 (5V), J5.47 (5V), RN3.1, U24.14 (VCC); also elsewhere on the board

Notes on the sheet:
ADDRESS BUS
DATA BUS
CONTROL BUS
Please note slots has no +12/-12 voltage rails. This is so becase it's rarely needed and it would complicate the design, needing a built-in AC/DC converter and voltage regulator.

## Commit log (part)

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2026-06-02 Update to KiCad v10 and use plugin-based Artemisa libs
2026-06-02 Add enclosure CAD files for 3D printing
2026-06-24 Fix GFX9918 backplate connector

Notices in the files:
motherboard-hk10.kicad_pcb:
Copyright(C) 2018-2026 Alvaro Polo
